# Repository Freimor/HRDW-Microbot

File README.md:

# Robot Library for ESP32S3-N16R8

Библиотека функций для робота на базе микроконтроллера **ESP32S3-N16R8**.

## Компоненты

| Компонент | Модель | Интерфейс |
|-----------|--------|-----------|
| Микроконтроллер | ESP32S3-N16R8 | - |
| Камера | OV5640 (DFRobot AI CAM) | DVP |
| Монитор батареи | LC709203F | I2C |
| АЦП для фоторезисторов | ADS1015 | I2C |
| Фоторезисторы | 4 шт | ADS1015 |
| Датчики линии | GP25700 (4 шт) | GPIO |
| Контроллер двигателей | DRV8834 | PWM + DIR |
| Энкодеры | OH137 (2 шт) | GPIO Interrupt |
| TOF дальномер | VL53L0X | I2C |
| Датчик освещенности | LTR-308 | I2C |
| Адресные светодиоды | SK6812 (4 шт) | GPIO |
| Buzzer | Пьезо | PWM |

## Структура проекта

```
robot-library/
├── include/
│   ├── robot_config.h      # Конфигурация пинов
│   └── robot_library.h     # Заголовочный файл библиотеки
├── src/
│   └── robot_library.cpp   # Реализация библиотеки
├── examples/
│   └── basic_example.ino   # Пример использования
└── README.md               # Этот файл
```

## Установка

1. Скопируйте папки `include` и `src` в ваш проект Arduino/PlatformIO
2. Для PlatformIO добавьте в `platformio.ini`:
   ```ini
   lib_deps = 
       pololu/vl53l0x
   build_flags = 
       -D USE_ESP_CAMERA
   ```

## Быстрый старт

```cpp
#include "robot_library.h"

void setup() {
    // Инициализация всех компонентов
    robot.begin();
}

void loop() {
    // Чтение датчиков
    float voltage = robot.getBatteryVoltage();
    uint16_t distance = robot.getDistanceMM();
    float lux = robot.getLux();
    
    // Управление двигателями
    robot.setMotorSpeed(100, 100); // Левый, Правый (-255 до 255)
    
    // Светодиоды
    robot.setAllLedsColor(255, 0, 0); // Красный цвет
    robot.showLeds();
    
    delay(1000);
}
```

## API Библиотеки

### Инициализация
- `bool begin()` - Инициализация всех компонентов

### Батарея (LC709203F)
- `float getBatteryVoltage()` - Напряжение батареи (В)
- `float getBatteryPercentage()` - Процент заряда (%)
- `bool isCharging()` - Статус зарядки

### Фоторезисторы (ADS1015)
- `PhotoResistorData getPhotoResistorData()` - Данные со всех 4 каналов
- `uint16_t getPhotoResistorValue(uint8_t channel)` - Значение канала (0-3)

### Датчики линии (GP25700)
- `LineSensorData getLineSensorData()` - Данные со всех датчиков
- `bool getLineSensorValue(uint8_t sensorNum)` - Значение датчика (1-4)
- `uint8_t getLinePosition()` - Позиция линии (0-3 или 255 если нет)

### Двигатели (DRV8834) + Энкодеры (OH137)
- `void setMotorSpeed(int16_t left, int16_t right)` - Установка скорости
- `void setLeftMotorSpeed(int16_t speed)` - Скорость левого мотора
- `void setRightMotorSpeed(int16_t speed)` - Скорость правого мотора
- `void stopMotors()` - Остановка двигателей
- `int32_t getLeftEncoderCount()` - Позиция левого энкодера
- `int32_t getRightEncoderCount()` - Позиция правого энкодера
- `void resetEncoders()` - Сброс энкодеров

### TOF дальномер (VL53L0X)
- `uint16_t getDistanceMM()` - Расстояние в мм
- `bool isDistanceValid()` - Валидность данных

### Датчик освещенности (LTR-308)
- `float getLux()` - Освещенность в Lux
- `bool isLightValid()` - Валидность данных

### Светодиоды (SK6812)
- `void setLedColor(uint8_t index, uint8_t r, uint8_t g, uint8_t b)` - Цвет светодиода
- `void setAllLedsColor(uint8_t r, uint8_t g, uint8_t b)` - Цвет всех светодиодов
- `void clearLeds()` - Выключить все
- `void showLeds()` - Обновить ленту
- `void setLedBrightness(uint8_t brightness)` - Яркость (0-255)

### Buzzer
- `void beep(uint16_t frequency, uint16_t duration_ms)` - Короткий сигнал
- `void playTone(uint16_t frequency, uint16_t duration_ms)` - Воспроизведение тона
- `void stopBuzzer()` - Остановить звук

### Камера (OV5640)
- `bool cameraInit()` - Инициализация камеры
- `bool cameraCapture()` - Захват кадра
- `void cameraDeinit()` - Деинициализация

## Конфигурация пинов

Пины настроены в файле `robot_config.h`. При необходимости измените под вашу схему.

## Зависимости

- **Arduino ESP32 Core** - базовая платформа
- **Wire.h** - I2C коммуникация (входит в core)
- **Pololu VL53L0X Library** (опционально) - для улучшенной работы TOF

## Лицензия

MIT License

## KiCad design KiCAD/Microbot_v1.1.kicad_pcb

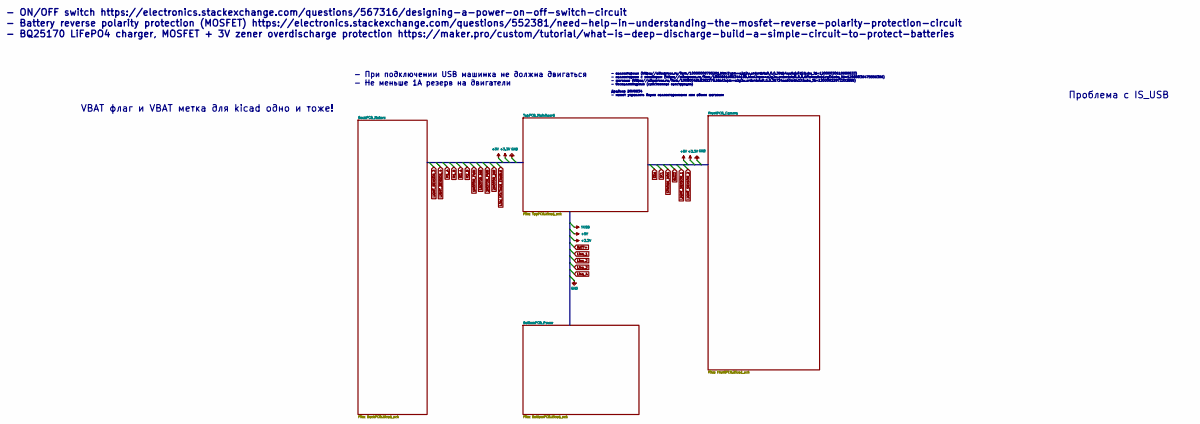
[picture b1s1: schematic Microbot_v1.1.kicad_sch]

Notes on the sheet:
- При подключении USB машинка не должна двигаться - Не меньше 1А резерв на двигатели
- ON/OFF switch https://electronics.stackexchange.com/questions/567316/designing-a-power-on-off-switch-circuit - Battery reverse polarity protection (MOSFET) https://electronics.stackexchange.com/questions/552381/need-help-in-understanding-the-mosfet-reverse-polarity-protection-circuit - BQ25170 Li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
Проблема с IS_USB
- коллекторные (https://aliexpress.ru/item/10000008795281.html?spm=a2g2w.orderdetail.0.0.39db4aa6xjxTd2&sku_id=12000030618959533) - коллекторные с энкодером (https://aliexpress.ru/item/1005001608344100.html?spm=a2g2w.orderdetail.0.0.6ffa4aa6xb1cgO&sku_id=12000036475556396) - шаговые (https://aliexp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
VBAT флаг и VBAT метка для kicad одно и тоже!

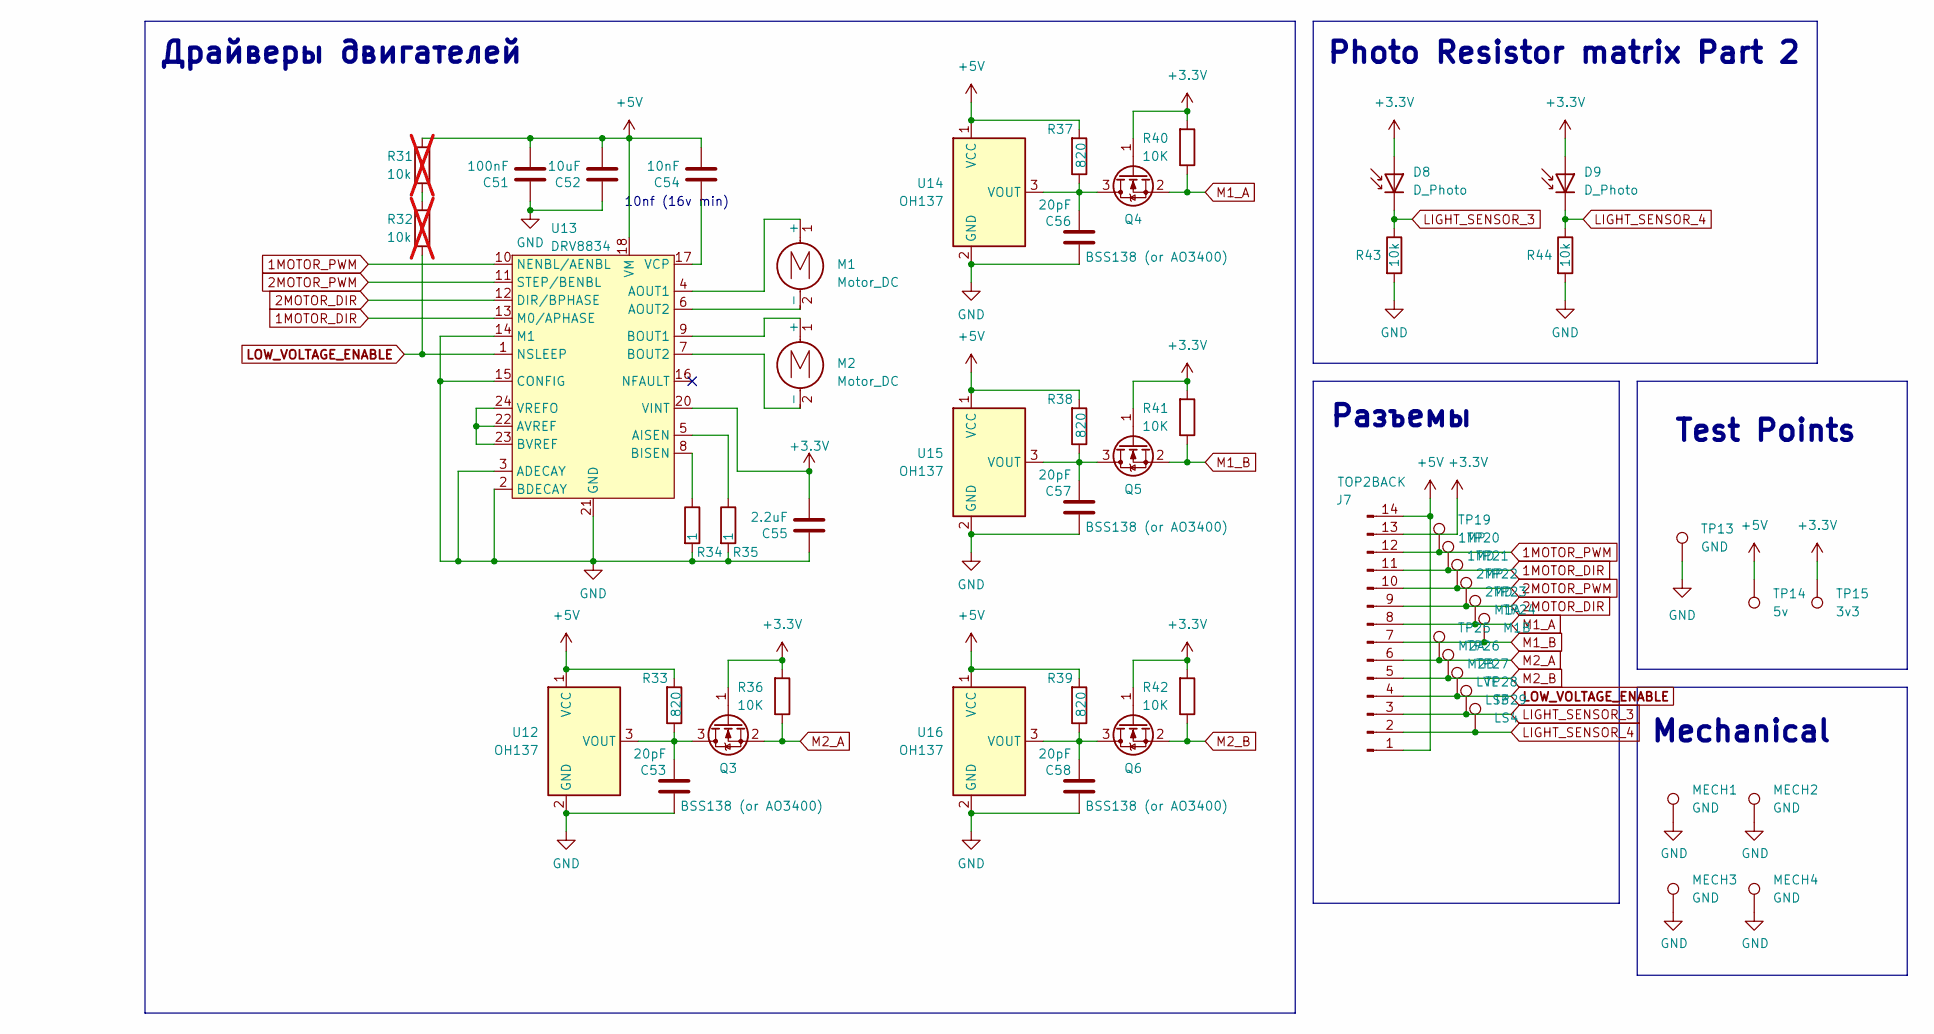
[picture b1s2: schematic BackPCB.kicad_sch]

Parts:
C51: 100nF; C_0402_1005Metric_Pad0.74x0.62mm_HandSolder
C52: 10uF; C_0603_1608Metric_Pad1.08x0.95mm_HandSolder
C53, C56, C57, C58: 20pF; C_0603_1608Metric_Pad1.08x0.95mm_HandSolder
C54: 10nF; C_0402_1005Metric_Pad0.74x0.62mm_HandSolder
C55: 2.2uF; C_0603_1608Metric_Pad1.08x0.95mm_HandSolder
D8, D9: D_Photo; Photoresistor_TH_Vertical
J7: TOP2BACK; CONN_14pin
M1, M2: Motor_DC; GW12-N20 with encoders PCB footprint
MECH1, MECH2, MECH3, MECH4: GND; CONN_PCB2PCB
Q3, Q4, Q5, Q6: BSS138 (or AO3400); SOT-23
R31, R32: 10k; R_0402_1005Metric_Pad0.72x0.64mm_HandSolder; not fitted
R33, R37, R38, R39: 820; R_0402_1005Metric_Pad0.72x0.64mm_HandSolder
R34, R35: 1; R_1206_3216Metric_Pad1.30x1.75mm_HandSolder
R36, R40, R41, R42: 10K; R_0402_1005Metric_Pad0.72x0.64mm_HandSolder
R43, R44: 10k; R_0402_1005Metric_Pad0.72x0.64mm_HandSolder
TP13: GND; TestPoint_Pad_D2.0mm
TP14: 5v; TestPoint_Pad_D2.0mm
TP15: 3v3; TestPoint_Pad_D2.0mm
TP19: 1MP; TestPoint_Pad_D1.0mm
TP20: 1MD; TestPoint_Pad_D1.0mm
TP21: 2MP; TestPoint_Pad_D1.0mm
TP22: 2MD; TestPoint_Pad_D1.0mm
TP23: M1A; TestPoint_Pad_D1.0mm
TP24: M1B; TestPoint_Pad_D1.0mm
TP25: M2A; TestPoint_Pad_D1.0mm
TP26: M2B; TestPoint_Pad_D1.0mm
TP27: LVE; TestPoint_Pad_D1.0mm
TP28: LS3; TestPoint_Pad_D1.0mm
TP29: LS4; TestPoint_Pad_D1.0mm
U12, U14, U15, U16: OH137; TO-92S
U13: DRV8834; HTSSOP-24-1EP_4.4x7.8mm_P0.65mm_EP3.4x7.8mm_Mask2.4x2.98mm

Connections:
1MOTOR_DIR: J7.11, TP20.1, U13.13 (M0/APHASE); also elsewhere on the board
1MOTOR_PWM: J7.12, TP19.1, U13.10 (NENBL/AENBL); also elsewhere on the board
2MOTOR_DIR: J7.9, TP22.1, U13.12 (DIR/BPHASE); also elsewhere on the board
2MOTOR_PWM: J7.10, TP21.1, U13.11 (STEP/BENBL); also elsewhere on the board
+3.3V: C55.2, D8.2 (A), D9.2 (A), J7.13, Q3.1 (G), Q4.1 (G), Q5.1 (G), Q6.1 (G), R36.2, R40.2, R41.2, R42.2, TP15.1, U13.20 (VINT); also elsewhere on the board
+5V: C51.2, C52.2, C54.2, J7.1, J7.14, R31.1, R33.2, R37.2, R38.2, R39.2, TP14.1, U12.1 (VCC), U13.18 (VM), U13.19 (VM), U14.1 (VCC), U15.1 (VCC), U16.1 (VCC); also elsewhere on the board
GND: C51.1, C52.1, C53.1, C55.1, C56.1, C57.1, C58.1, MECH1.1, MECH2.1, MECH3.1, MECH4.1, R34.2, R35.2, R43.2, R44.2, TP13.1, U12.2 (GND), U13.2 (BDECAY), U13.3 (ADECAY), U13.14 (M1), U13.15 (CONFIG), U13.21 (GND), U13.25, U14.2 (GND), U15.2 (GND), U16.2 (GND); also elsewhere on the board
LIGHT_SENSOR_3: D8.1 (K), J7.3, R43.1, TP28.1; also elsewhere on the board
LIGHT_SENSOR_4: D9.1 (K), J7.2, R44.1, TP29.1; also elsewhere on the board
LOW_VOLTAGE_ENABLE: J7.4, R32.2, TP27.1, U13.1 (NSLEEP); also elsewhere on the board
M1_A: J7.8, Q4.2 (S), R40.1, TP23.1; also elsewhere on the board
M1_B: J7.7, Q5.2 (S), R41.1, TP24.1; also elsewhere on the board
M2_A: J7.6, Q3.2 (S), R36.1, TP25.1; also elsewhere on the board
M2_B: J7.5, Q6.2 (S), R42.1, TP26.1; also elsewhere on the board
unnamed: M2.1 (+), U13.9 (BOUT1)
unnamed: M2.2 (-), U13.7 (BOUT2)
unnamed: C53.2, Q3.3 (D), R33.1, U12.3 (VOUT)
unnamed: C56.2, Q4.3 (D), R37.1, U14.3 (VOUT)
unnamed: C57.2, Q5.3 (D), R38.1, U15.3 (VOUT)
unnamed: C58.2, Q6.3 (D), R39.1, U16.3 (VOUT)
unnamed: R31.2, R32.1
unnamed: R35.1, U13.5 (AISEN)
unnamed: U13.22 (AVREF), U13.23 (BVREF), U13.24 (VREFO)
unnamed: R34.1, U13.8 (BISEN)
unnamed: C54.1, U13.17 (VCP)

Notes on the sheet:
10nf (16v min)
Photo Resistor matrix Part 2
Mechanical
Test Points
Драйверы двигателей
Разъемы

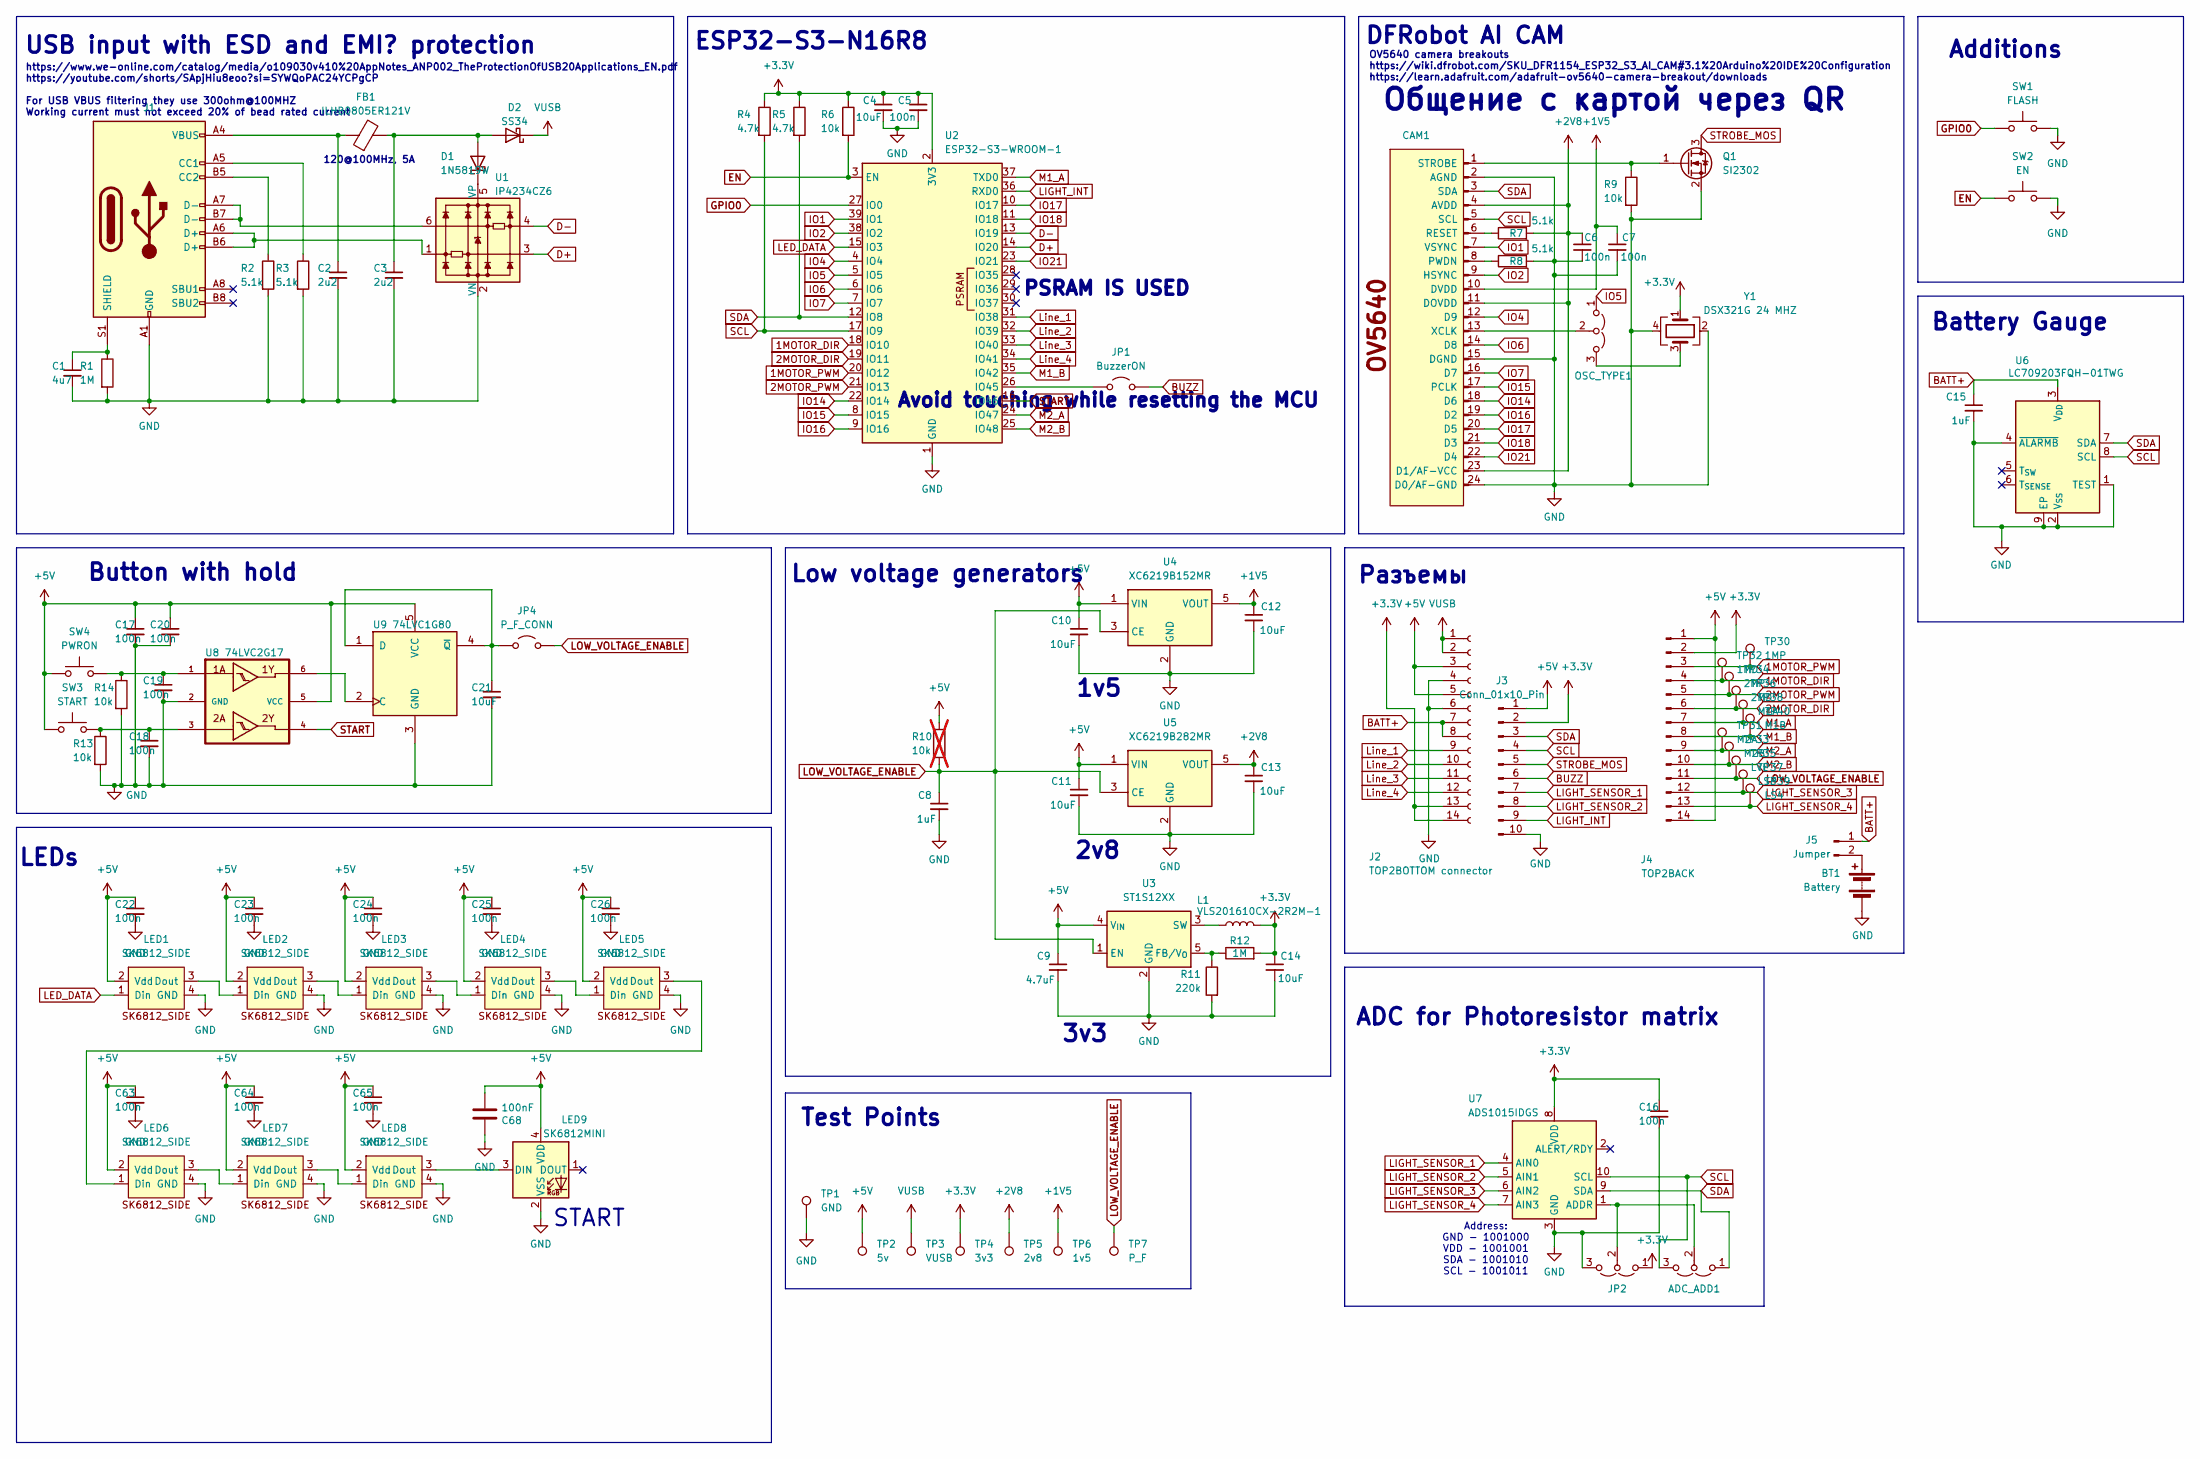
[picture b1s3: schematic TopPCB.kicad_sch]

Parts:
ADC_ADD1: Jumper_3_Open; SolderJumper-3_P1.3mm_Open_RoundedPad1.0x1.5mm_NumberLabels
BT1: Battery; Conn_Molex_2026560021(Pico-EZmate_Slim)
C1: 4u7; C_0603_1608Metric_Pad1.08x0.95mm_HandSolder
C2, C3: 2u2; C_0603_1608Metric_Pad1.08x0.95mm_HandSolder
C4, C21: 10uF; C_0603_1608Metric
C5, C6, C7, C16, C17, C18, C19, C20, C22, C23, C24, C25, C26, C63, C64, C65: 100n; C_0402_1005Metric_Pad0.74x0.62mm_HandSolder
C8, C15: 1uF; C_0603_1608Metric_Pad1.08x0.95mm_HandSolder
C9: 4.7uF; C_0603_1608Metric_Pad1.08x0.95mm_HandSolder
C10, C11, C12, C13, C14: 10uF; C_0603_1608Metric_Pad1.08x0.95mm_HandSolder
C68: 100nF; C_0402_1005Metric_Pad0.74x0.62mm_HandSolder
CAM1: OV5640; CAM_OV5640_OMRON_XF2M-2415-1A
D1: 1N5819W; D_SOD-123
D2: SS34; D_SMA_Handsoldering
FB1: ILHB0805ER121V; L_0805_2012Metric_Pad1.15x1.40mm_HandSolder
J1: USB_C_Receptacle_USB2.0; RUICHI_TYPE-C-16PF-020
J2: TOP2BOTTOM connector; PinHeader_2x07_P2.54mm_Vertical_SMD
J3: Conn_01x10_Pin; CONN_10pin
J4: TOP2BACK; CONN_14pin
J5: Jumper; PinHeader_1x02_P2.54mm_Vertical
JP1: BuzzerON; SolderJumper-2_P1.3mm_Open_RoundedPad1.0x1.5mm
JP2: Jumper_3_Open; SolderJumper-3_P1.3mm_Open_RoundedPad1.0x1.5mm_NumberLabels
JP4: P_F_CONN; SolderJumper-2_P1.3mm_Open_RoundedPad1.0x1.5mm
L1: VLS201610CX-2R2M-1; IND_VLS201610CX-220M-1
LED1, LED2, LED3, LED4, LED5, LED6, LED7, LED8: SK6812_SIDE; ADR_LED_SK6812_SIDE
LED9: SK6812MINI; LED_SK6812MINI_PLCC4_3.5x3.5mm_P1.75mm
OSC_TYPE1: OSC_IN/EX; SolderJumper-3_P1.3mm_Open_RoundedPad1.0x1.5mm_NumberLabels
Q1: SI2302; SOT-23
R1, R12: 1M; R_0402_1005Metric_Pad0.72x0.64mm_HandSolder
R2, R3, R7, R8: 5.1k; R_0402_1005Metric_Pad0.72x0.64mm_HandSolder
R4, R5: 4.7k; R_0402_1005Metric_Pad0.72x0.64mm_HandSolder
R6, R9, R13, R14: 10k; R_0402_1005Metric_Pad0.72x0.64mm_HandSolder
R10: 10k; R_0402_1005Metric_Pad0.72x0.64mm_HandSolder; not fitted
R11: 220k; R_0402_1005Metric_Pad0.72x0.64mm_HandSolder
SW1: FLASH; SW_SMD_KLS7-TS3401
SW2: EN; SW_SMD_KLS7-TS3401
SW3: START; SW_SMD_KLS7-TS3401
SW4: PWRON; SW_SMD_KLS7-TS3401
TP1: GND; TestPoint_Pad_D2.0mm
TP2: 5v; TestPoint_Pad_D2.0mm
TP3: VUSB; TestPoint_Pad_D2.0mm
TP4: 3v3; TestPoint_Pad_D2.0mm
TP5: 2v8; TestPoint_Pad_D2.0mm
TP6: 1v5; TestPoint_Pad_D2.0mm
TP7: P_F; TestPoint_Pad_D2.0mm
TP30: 1MP; TestPoint_Pad_D1.0mm
TP31: M2A; TestPoint_Pad_D1.0mm
TP32: 1MD; TestPoint_Pad_D1.0mm
TP33: M2B; TestPoint_Pad_D1.0mm
TP34: 2MP; TestPoint_Pad_D1.0mm
TP35: LVE; TestPoint_Pad_D1.0mm
TP36: 2MD; TestPoint_Pad_D1.0mm
TP37: LS3; TestPoint_Pad_D1.0mm
TP38: M1A; TestPoint_Pad_D1.0mm
TP39: LS4; TestPoint_Pad_D1.0mm
TP40: M1B; TestPoint_Pad_D1.0mm
U1: IP4234CZ6; SC-74-6_1.55x2.9mm_P0.95mm
U2: ESP32-S3-WROOM-1
U3: ST1S12XX; TSOT-23-5
U4: XC6219B152MR; SOT-23-5
U5: XC6219B282MR; SOT-23-5
U6: LC709203FQH-01TWG; WDFN-8-1EP_4x3mm_P0.65mm_EP2.4x1.8mm
U7: ADS1015IDGS; TSSOP-10_3x3mm_P0.5mm
U8: 74LVC2G17; SOT-23-6_Handsoldering
U9: 74LVC1G80
Y1: DSX321G 24 MHZ; Crystal_SMD_3225-4Pin_3.2x2.5mm_HandSoldering

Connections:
1MOTOR_DIR: J4.4, TP32.1, U2.18 (IO10); also elsewhere on the board
1MOTOR_PWM: J4.3, TP30.1, U2.20 (IO12); also elsewhere on the board
2MOTOR_DIR: J4.6, TP36.1, U2.19 (IO11); also elsewhere on the board
2MOTOR_PWM: J4.5, TP34.1, U2.21 (IO13); also elsewhere on the board
+1V5: C7.1, C12.1, CAM1.10 (DVDD), TP6.1, U4.5 (VOUT)
+2V8: C6.1, C13.1, CAM1.4 (AVDD), CAM1.11 (DOVDD), CAM1.23 (D1/AF-VCC), R7.2, TP5.1, U5.5 (VOUT)
+3.3V: C4.1, C5.1, C14.1, C16.1, J2.13, J2.14, J3.2, J4.2, JP2.1 (A), L1.2, R4.1, R5.1, R6.1, R12.2, TP4.1, U2.2 (3V3), U7.8 (VDD), Y1.1; also elsewhere on the board
+5V: C9.1, C10.1, C11.1, C17.1, C20.1, C22.1, C23.1, C24.1, C25.1, C26.1, C63.1, C64.1, C65.1, C68.2, J2.3, J2.5, J3.1, J4.1, J4.14, LED1.2 (Vdd), LED2.2 (Vdd), LED3.2 (Vdd), LED4.2 (Vdd), LED5.2 (Vdd), LED6.2 (Vdd), LED7.2 (Vdd), LED8.2 (Vdd), LED9.4 (VDD), R10.1, SW3.1, SW4.1, TP2.1, U3.4 (V_{IN}), U4.1 (VIN), U5.1 (VIN), U8.5 (VCC), U9.5 (VCC); also elsewhere on the board
BATT+: C15.1, J2.7, J2.8, J5.1, U6.3 (V_{DD}); also elsewhere on the board
BUZZ: J3.6, JP1.2 (B); also elsewhere on the board
D+: U1.3, U2.14 (IO20)
D-: U1.4, U2.13 (IO19)
EN: R6.2, SW2.1, U2.3 (EN)
GND: BT1.2 (-), C1.2, C2.2, C3.2, C4.2, C5.2, C6.2, C7.2, C8.2, C9.2, C10.2, C11.2, C12.2, C13.2, C14.2, C15.2, C16.2, C17.2, C18.2, C19.2, C20.2, C21.2, C22.2, C23.2, C24.2, C25.2, C26.2, C63.2, C64.2, C65.2, C68.1, CAM1.2 (AGND), CAM1.15 (DGND), CAM1.24 (D0/AF-GND), CAM1.P1, CAM1.P2, J1.A1 (GND), J1.A12 (GND), J1.B1 (GND), J1.B12 (GND), J2.4, J2.6, J3.10, JP2.3 (B), LED1.4 (GND), LED2.4 (GND), LED3.4 (GND), LED4.4 (GND), LED5.4 (GND), LED6.4 (GND), LED7.4 (GND), LED8.4 (GND), LED9.2 (VSS), Q1.2 (S), R1.2, R2.2, R3.2, R8.2, R9.2, R11.2, R13.2, R14.2, SW1.2, SW2.2, TP1.1, U1.2 (VN), U2.1 (GND), U2.40 (GND), U2.41 (GND), U3.2 (GND), U4.2 (GND), U5.2 (GND), U6.1 (TEST), U6.2 (V_{SS}), U6.4 (~ALARMB), U6.9 (EP), U7.3 (GND), U8.2 (GND), U9.3 (GND), Y1.2, Y1.4; also elsewhere on the board
GPIO0: SW1.1, U2.27 (IO0)
IO1: CAM1.7 (VSYNC), U2.39 (IO1)
IO2: CAM1.9 (HSYNC), U2.38 (IO2)
IO4: CAM1.12 (D9), U2.4 (IO4)
IO5: OSC_TYPE1.1 (A), U2.5 (IO5)
IO6: CAM1.14 (D8), U2.6 (IO6)
IO7: CAM1.16 (D7), U2.7 (IO7)
IO14: CAM1.18 (D6), U2.22 (IO14)
IO15: CAM1.17 (PCLK), U2.8 (IO15)
IO16: CAM1.19 (D2), U2.9 (IO16)
IO17: CAM1.20 (D5), U2.10 (IO17)
IO18: CAM1.21 (D3), U2.11 (IO18)
IO21: CAM1.22 (D4), U2.23 (IO21)
LED_DATA: LED1.1 (Din), U2.15 (IO3)
LIGHT_INT: J3.9, U2.36 (RXD0); also elsewhere on the board
LIGHT_SENSOR_1: J3.7, U7.4 (AIN0); also elsewhere on the board
LIGHT_SENSOR_2: J3.8, U7.5 (AIN1); also elsewhere on the board
LIGHT_SENSOR_3: J4.12, TP37.1, U7.6 (AIN2); also elsewhere on the board
LIGHT_SENSOR_4: J4.13, TP39.1, U7.7 (AIN3); also elsewhere on the board
LOW_VOLTAGE_ENABLE: C8.1, J4.11, JP4.2 (B), R10.2, TP7.1, TP35.1, U3.1 (EN), U4.3 (CE), U5.3 (CE); also elsewhere on the board
Line_1: J2.9, U2.31 (IO38); also elsewhere on the board
Line_2: J2.10, U2.32 (IO39); also elsewhere on the board
Line_3: J2.11, U2.33 (IO40); also elsewhere on the board
Line_4: J2.12, U2.34 (IO41); also elsewhere on the board
M1_A: J4.7, TP38.1, U2.37 (TXD0); also elsewhere on the board
M1_B: J4.8, TP40.1, U2.35 (IO42); also elsewhere on the board
M2_A: J4.9, TP31.1, U2.24 (IO47); also elsewhere on the board
M2_B: J4.10, TP33.1, U2.25 (IO48); also elsewhere on the board
unnamed: ADC_ADD1.2 (C), JP2.2 (C), U7.1 (ADDR)
unnamed: BT1.1 (+), J5.2
unnamed: C2.1, FB1.1, J1.A4 (VBUS), J1.A9 (VBUS), J1.B4 (VBUS), J1.B9 (VBUS)
unnamed: C18.1, R13.1, SW3.2, U8.3
unnamed: C19.1, R14.1, SW4.2, U8.1
unnamed: CAM1.8 (PWDN), R8.1
unnamed: CAM1.6 (RESET), R7.1
unnamed: CAM1.1 (STROBE), Q1.1 (G), R9.1
unnamed: CAM1.13 (XCLK), OSC_TYPE1.2 (C)
unnamed: C3.1, D1.2 (A), D2.2 (A), FB1.2
unnamed: D1.1 (K), U1.5 (VP)
unnamed: J1.A5 (CC1), R3.1
unnamed: J1.B5 (CC2), R2.1
unnamed: J1.A6 (D+), J1.B6 (D+), U1.1
unnamed: J1.A7 (D-), J1.B7 (D-), U1.6
unnamed: C1.1, J1.S1 (SHIELD), R1.1
unnamed: JP1.1 (A), U2.26 (IO45)
unnamed: C21.1, JP4.1 (A), U9.1 (D), U9.4 (~Q)
unnamed: LED1.3 (Dout), LED2.1 (Din)
unnamed: LED2.3 (Dout), LED3.1 (Din)
unnamed: LED3.3 (Dout), LED4.1 (Din)
unnamed: LED4.3 (Dout), LED5.1 (Din)
unnamed: LED5.3 (Dout), LED6.1 (Din)
unnamed: LED6.3 (Dout), LED7.1 (Din)
unnamed: LED7.3 (Dout), LED8.1 (Din)
unnamed: LED8.3 (Dout), LED9.3 (DIN)
unnamed: OSC_TYPE1.3 (B), Y1.3
unnamed: R11.1, R12.1, U3.5 (FB/V_{O})
unnamed: L1.1, U3.3 (SW)
unnamed: U8.6, U9.2 (C)
SCL: ADC_ADD1.3 (B), CAM1.5 (SCL), J3.4, R4.2, U2.17 (IO9), U6.8 (SCL), U7.10 (SCL); also elsewhere on the board
SDA: ADC_ADD1.1 (A), CAM1.3 (SDA), J3.3, R5.2, U2.12 (IO8), U6.7 (SDA), U7.9 (SDA); also elsewhere on the board
START: U2.16 (IO46), U8.4
STROBE_MOS: J3.5, Q1.3 (D); also elsewhere on the board
VUSB: D2.1 (K), J2.1, J2.2, TP3.1; also elsewhere on the board

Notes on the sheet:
ADC for Photoresistor matrix
LEDs
120@100MHz, 5A
Общение с картой через QR
Avoid touching while resetting the MCU
Разъемы
OV5640 camera breakouts https://wiki.dfrobot.com/SKU_DFR1154_ESP32_S3_AI_CAM#3.1%20Arduino%20IDE%20Configuration https://learn.adafruit.com/adafruit-ov5640-camera-breakout/downloads
DFRobot AI CAM
Test Points
3v3
2v8
PSRAM IS USED
1v5
Low voltage generators
START
Button with hold
Battery Gauge
Additions
https://www.we-online.com/catalog/media/o109030v410%20AppNotes_ANP002_TheProtectionOfUSB20Applications_EN.pdf https://youtube.com/shorts/SApjHiu8eoo?si=SYWQoPAC24YCPgCP For USB VBUS filtering they use 300ohm@100MHZ Working current must not exceed 20% of bead rated current
USB input with ESD and EMI? protection
ESP32-S3-N16R8
Address: GND - 1001000 VDD - 1001001 SDA - 1001010 SCL - 1001011

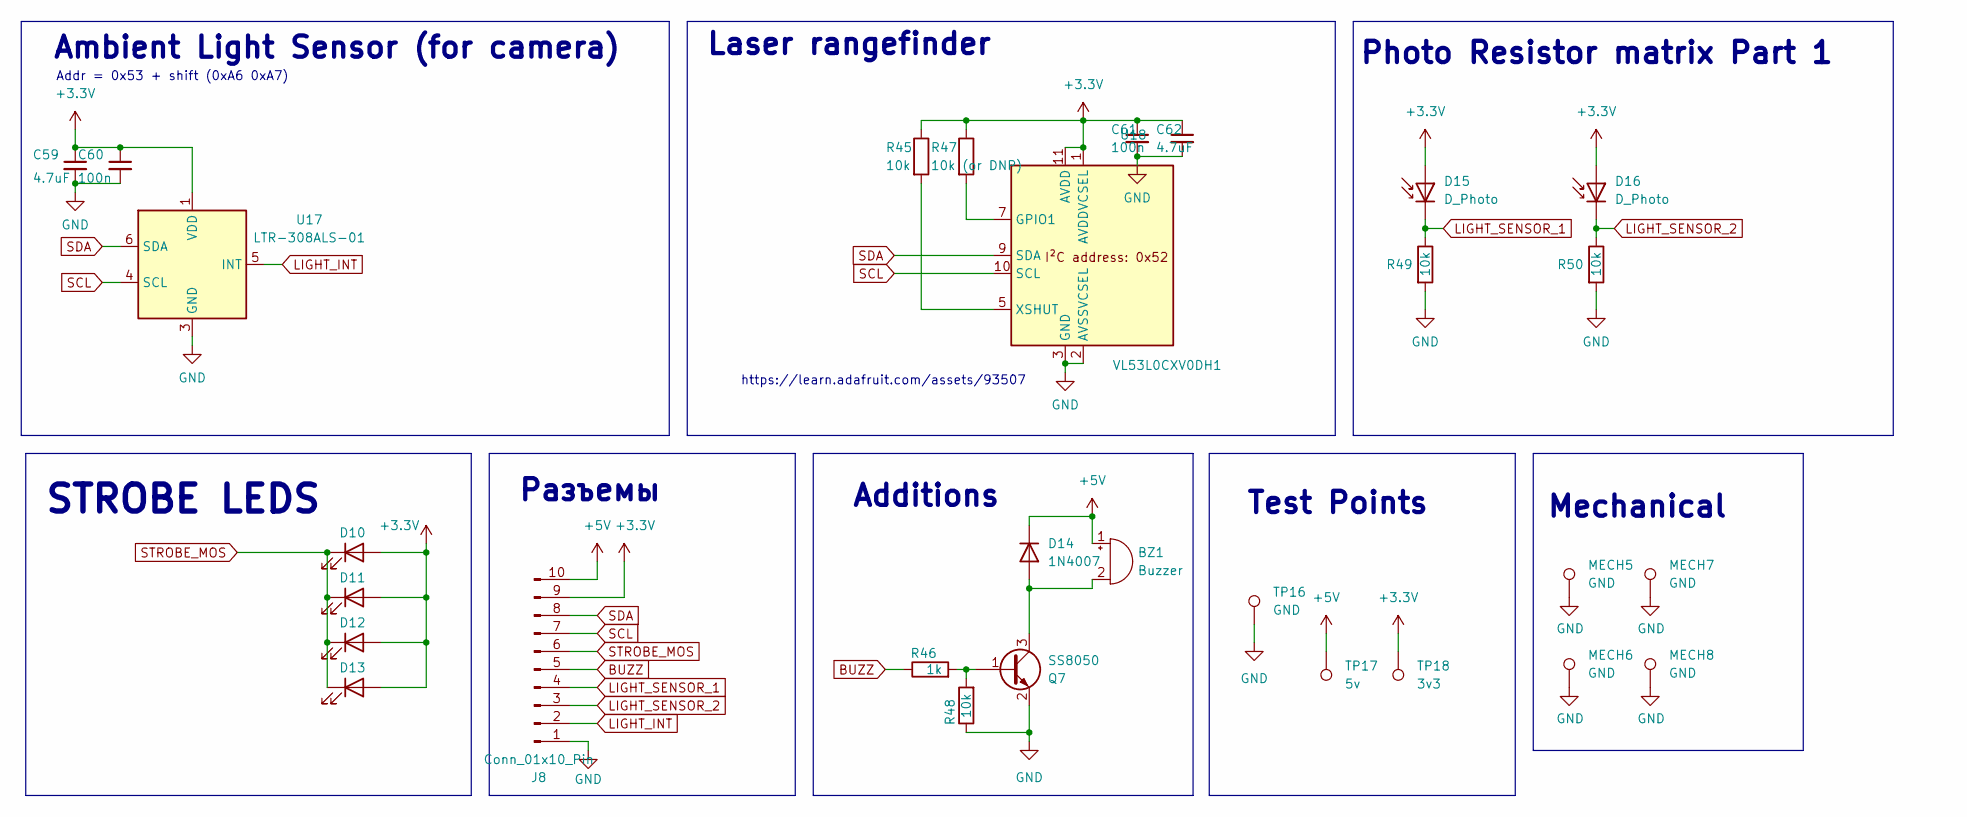
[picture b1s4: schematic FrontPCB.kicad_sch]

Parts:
BZ1: Buzzer; PASSIVE_SMD_MLT-8530
C59, C62: 4.7uF; C_0603_1608Metric
C60, C61: 100n; C_0402_1005Metric_Pad0.74x0.62mm_HandSolder
D10, D11, D12, D13: HL-A-2835H358W-2-S1-08L-HR3; LED_Everlight-SMD3528_3.5x2.8mm_67-21ST
D14: 1N4007; D_SOD-123F
D15, D16: D_Photo; Photoresistor_TH_Vertical
J8: Conn_01x10_Pin; CONN_10pin
MECH5, MECH6, MECH7, MECH8: GND; CONN_PCB2PCB
Q7: SS8050; SOT-23
R45, R48, R49, R50: 10k; R_0402_1005Metric_Pad0.72x0.64mm_HandSolder
R46: 1k; R_0402_1005Metric_Pad0.72x0.64mm_HandSolder
R47: 10k (or DNP); R_0402_1005Metric_Pad0.72x0.64mm_HandSolder
TP16: GND; TestPoint_Pad_D2.0mm
TP17: 5v; TestPoint_Pad_D2.0mm
TP18: 3v3; TestPoint_Pad_D2.0mm
U17: LTR-308ALS-01; LightSensor_LTR-303ALS-01
U18: VL53L0CXV0DH1; ToF_LaserRange_VL53L0X_StandartFootprint

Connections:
+3.3V: C59.1, C60.1, C61.1, C62.1, D10.2 (A), D11.2 (A), D12.2 (A), D13.2 (A), D15.2 (A), D16.2 (A), J8.9, R45.1, R47.1, TP18.1, U17.1 (VDD), U18.1 (AVDDVCSEL), U18.11 (AVDD); also elsewhere on the board
+5V: BZ1.1 (-), D14.1 (K), J8.10, TP17.1; also elsewhere on the board
BUZZ: J8.5, R46.1; also elsewhere on the board
GND: C59.2, C60.2, C61.2, C62.2, J8.1, MECH5.1, MECH6.1, MECH7.1, MECH8.1, Q7.2 (E), R48.1, R49.2, R50.2, TP16.1, U17.3 (GND), U18.2 (AVSSVCSEL), U18.3 (GND), U18.4 (GND), U18.6 (GND), U18.12 (GND); also elsewhere on the board
LIGHT_INT: J8.2, U17.5 (INT); also elsewhere on the board
LIGHT_SENSOR_1: D15.1 (K), J8.4, R49.1; also elsewhere on the board
LIGHT_SENSOR_2: D16.1 (K), J8.3, R50.1; also elsewhere on the board
unnamed: BZ1.2 (+), D14.2 (A), Q7.3 (C)
unnamed: Q7.1 (B), R46.2, R48.2
unnamed: R47.2, U18.7 (GPIO1)
unnamed: R45.2, U18.5 (XSHUT)
SCL: J8.7, U17.4 (SCL), U18.10 (SCL); also elsewhere on the board
SDA: J8.8, U17.6 (SDA), U18.9 (SDA); also elsewhere on the board
STROBE_MOS: D10.1 (K), D11.1 (K), D12.1 (K), D13.1 (K), J8.6; also elsewhere on the board

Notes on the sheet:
Mechanical
Test Points
Photo Resistor matrix Part 1
STROBE LEDS
Laser rangefinder
Ambient Light Sensor (for camera)
Addr = 0x53 + shift (0xA6 0xA7)
Additions
Разъемы
https://learn.adafruit.com/assets/93507

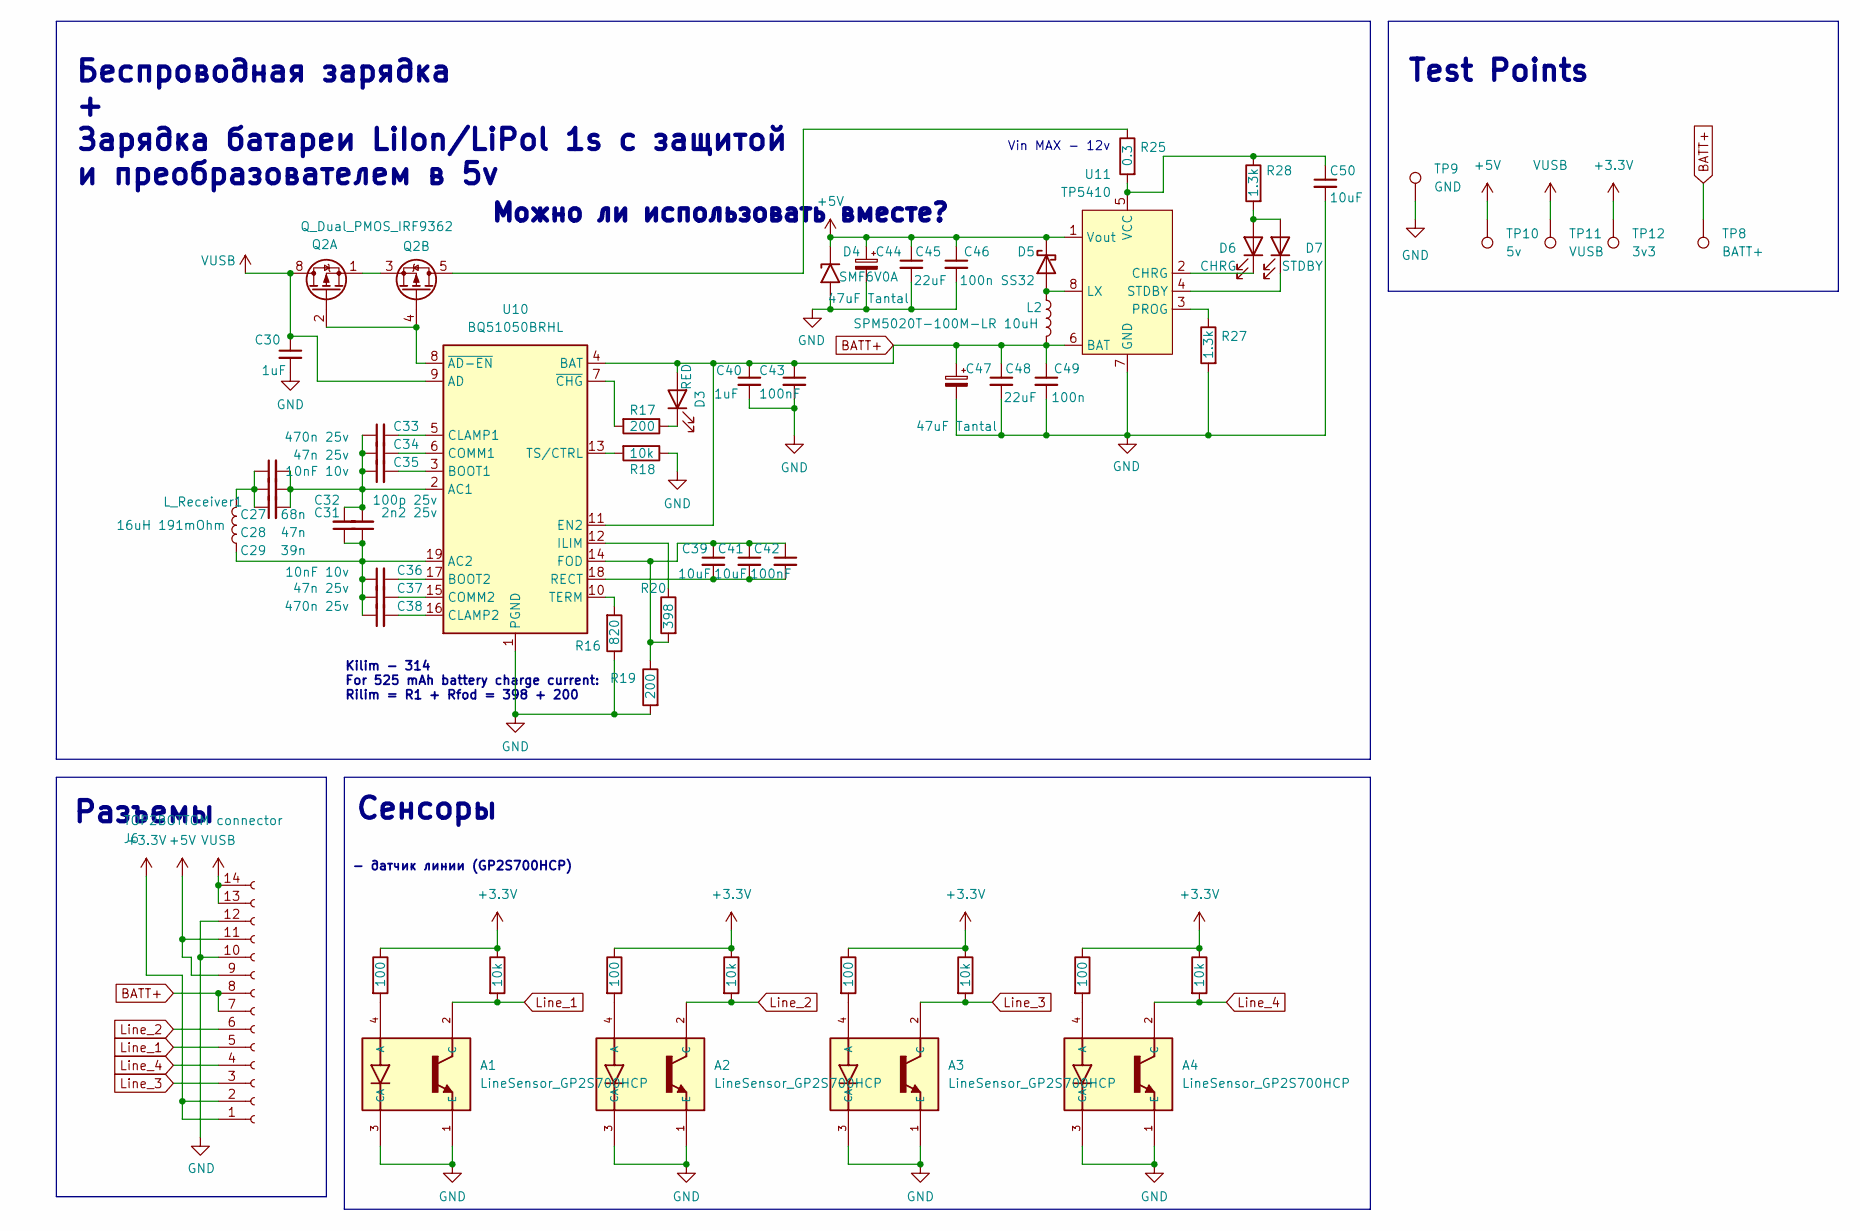
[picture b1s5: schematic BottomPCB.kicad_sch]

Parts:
A1, A2, A3, A4: LineSensor_GP2S700HCP; GP2S700HCP; PARTREV Oct. 3. 2005
C27: 68n; C_0402_1005Metric_Pad0.74x0.62mm_HandSolder
C28: 47n; C_0402_1005Metric_Pad0.74x0.62mm_HandSolder
C29: 39n; C_0402_1005Metric_Pad0.74x0.62mm_HandSolder
C30: 1uF; C_0603_1608Metric_Pad1.08x0.95mm_HandSolder
C31: 2n2 25v; C_0402_1005Metric_Pad0.74x0.62mm_HandSolder
C32: 100p 25v; C_0402_1005Metric_Pad0.74x0.62mm_HandSolder
C33, C38: 470n 25v; C_0402_1005Metric_Pad0.74x0.62mm_HandSolder
C34, C37: 47n 25v; C_0402_1005Metric_Pad0.74x0.62mm_HandSolder
C35, C36: 10nF 10v; C_0402_1005Metric_Pad0.74x0.62mm_HandSolder
C39, C41: 10uF; C_0603_1608Metric
C40: 1uF; C_0603_1608Metric
C42, C43: 100nF; C_0402_1005Metric_Pad0.74x0.62mm_HandSolder
C44, C47: 47uF Tantal; CP_EIA-7343-31_Kemet-D
C45, C48: 22uF; C_0805_2012Metric_Pad1.18x1.45mm_HandSolder
C46, C49: 100n; C_0402_1005Metric_Pad0.74x0.62mm_HandSolder
C50: 10uF; C_0603_1608Metric_Pad1.08x0.95mm_HandSolder
D3: RED; LED_SIDE_KA-2810_Kingbright
D4: SMF6V0A; D_SOD-123F
D5: SS32; D_SMA-SMB_Universal_Handsoldering
D6: CHRG; LED_SIDE_KA-2810_Kingbright
D7: STDBY; LED_SIDE_KA-2810_Kingbright
J6: TOP2BOTTOM connector; PinHeader_2x07_P2.54mm_Vertical_SMD
L2: SPM5020T-100M-LR 10uH; INDUCTOR_SPM5020T
L_Receiver1: 16uH 191mOhm; COIL
Q2: Q_Dual_PMOS_IRF9362; SOP-8_3.76x4.96mm_P1.27mm
R15, R22, R24, R29: 100; R_0805_2012Metric_Pad1.20x1.40mm_HandSolder
R16: 820; R_0402_1005Metric_Pad0.72x0.64mm_HandSolder
R17, R19: 200; R_0402_1005Metric_Pad0.72x0.64mm_HandSolder
R18, R21, R23, R26, R30: 10k; R_0402_1005Metric_Pad0.72x0.64mm_HandSolder
R20: 398; R_0402_1005Metric_Pad0.72x0.64mm_HandSolder
R25: 0.3; R_1210_3225Metric_Pad1.30x2.65mm_HandSolder
R27, R28: 1.3k; R_0402_1005Metric_Pad0.72x0.64mm_HandSolder
TP8: BATT+; TestPoint_Pad_D2.0mm
TP9: GND; TestPoint_Pad_D2.0mm
TP10: 5v; TestPoint_Pad_D2.0mm
TP11: VUSB; TestPoint_Pad_D2.0mm
TP12: 3v3; TestPoint_Pad_D2.0mm
U10: BQ51050BRHL; Texas_VQFN-RHL-20
U11: TP5410

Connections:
+3.3V: J6.1, J6.2, R15.1, R21.1, R22.1, R23.1, R24.1, R26.1, R29.1, R30.1, TP12.1; also elsewhere on the board
+5V: C44.1, C45.1, C46.1, D4.1 (A1), D5.1 (K), J6.9, J6.11, TP10.1, U11.1 (Vout); also elsewhere on the board
BATT+: C40.1, C43.1, C47.1, C48.1, C49.1, D3.2 (A), J6.7, J6.8, L2.1, TP8.1, U10.4 (BAT), U10.11 (EN2), U11.6 (BAT); also elsewhere on the board
GND: A1.1 (E), A1.3 (CA), A2.1 (E), A2.3 (CA), A3.1 (E), A3.3 (CA), A4.1 (E), A4.3 (CA), C30.2, C40.2, C43.2, C44.2, C45.2, C46.2, C47.2, C48.2, C49.2, C50.2, D4.2 (A2), J6.10, J6.12, R16.1, R18.1, R19.2, R27.2, TP9.1, U10.1 (PGND), U10.20 (PGND), U10.21 (PGND), U11.7 (GND), U11.9; also elsewhere on the board
Line_1: A1.2 (C), J6.5, R21.2; also elsewhere on the board
Line_2: A2.2 (C), J6.6, R23.2; also elsewhere on the board
Line_3: A3.2 (C), J6.3, R26.2; also elsewhere on the board
Line_4: A4.2 (C), J6.4, R30.2; also elsewhere on the board
unnamed: A1.4 (A), R15.2
unnamed: A2.4 (A), R22.2
unnamed: A3.4 (A), R24.2
unnamed: A4.4 (A), R29.2
unnamed: C27.1, C28.1, C29.1, L_Receiver1.2
unnamed: D3.1 (K), R17.1
unnamed: D5.2 (A), L2.2, U11.8 (LX)
unnamed: D6.2 (A), D7.2 (A), R28.2
unnamed: D6.1 (K), U11.2 (CHRG)
unnamed: D7.1 (K), U11.4 (STDBY)
unnamed: Q2.2 (G), Q2.4 (G), U10.8 (~AD-EN)
unnamed: Q2.1 (S), Q2.3 (S)
unnamed: Q2.5 (D), Q2.6 (D), R25.1
unnamed: C27.2, C28.2, C29.2, C31.2, C32.2, C33.1, C34.1, C35.1, U10.2 (AC1)
unnamed: C31.1, C32.1, C36.1, C37.1, C38.1, L_Receiver1.1, U10.19 (AC2)
unnamed: C35.2, U10.3 (BOOT1)
unnamed: C36.2, U10.17 (BOOT2)
unnamed: C33.2, U10.5 (CLAMP1)
unnamed: C38.2, U10.16 (CLAMP2)
unnamed: C34.2, U10.6 (COMM1)
unnamed: C37.2, U10.15 (COMM2)
unnamed: C39.1, C41.1, C42.1, R19.1, R20.2, U10.14 (FOD)
unnamed: R20.1, U10.12 (ILIM)
unnamed: C39.2, C41.2, C42.2, U10.18 (RECT)
unnamed: R16.2, U10.10 (TERM)
unnamed: R18.2, U10.13 (TS/CTRL)
unnamed: R17.2, U10.7 (~CHG)
unnamed: R27.1, U11.3 (PROG)
unnamed: C50.1, R25.2, R28.1, U11.5 (VCC)
VUSB: C30.1, J6.13, J6.14, Q2.7 (D), Q2.8 (D), TP11.1, U10.9 (AD); also elsewhere on the board

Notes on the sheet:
- датчик линии (GP2S700HCP)
Беспроводная зарядка + Зарядка батареи LiIon/LiPol 1s с защитой и преобразователем в 5v
Test Points
Можно ли использовать вместе?
Сенсоры
Kilim - 314 For 525 mAh battery charge current: Rilim = R1 + Rfod = 398 + 200
Разъемы
Vin MAX - 12v

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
